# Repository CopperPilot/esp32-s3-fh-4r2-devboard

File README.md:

# ESP32-S3FH4R2 Tiny-LLM Development Board

A compact, 4-layer, breadboard-friendly (`27.00 × 56.20 mm`, `0.9"` / `22.86 mm` row spacing) development board engineered around the **Espressif `ESP32-S3FH4R2`** SoC (`QFN-56 7×7 mm`, **4 MB in-package Quad SPI Flash** + **2 MB in-package Quad SPI PSRAM**) for running embedded LLM inference workloads such as **`llama2.c` (260K-parameter model)** at 240 MHz.

---

## Visual Overview

| Isometric 3D Render | Top Copper & Assembly Render | Bottom Silkscreen & Plane Render |
|---|---|---|
|  |  |  |

---

## Validation & Manufacturing Readiness Summary

| Verification Suite | Tool / Platform | Result | Errors / Dangers | Warnings | Status |
|---|---|---|---|---|---|
| **Schematic ERC** | `kicad-cli sch erc` (KiCad 10.0.4) | **PASS** | `0` | `0` | 100% Clean |
| **Schematic Layout Audit** | CopperPilot `validate_schematic_layout` | **PASS** | `0` | `0` | 100% Clean |
| **PCB Design Rules Check (DRC)** | `kicad-cli pcb drc` (KiCad 10.0.4) | **PASS** | `0` (`0` unconnected) | `0` | 100% Routed (70 nets, 221 pads) |
| **Schematic-to-PCB Netlist Parity** | XML Netlist vs `.kicad_pcb` Audit | **PASS** | `0` mismatches | `0` | 54/54 Footprints, 221/221 Pins Matched |
| **JLCPCB Live DFM (JLCDFM)** | `jlcdfm.com` (27-Check 4-Layer Suite) | **PASS** | **`0` Dangers** | **`0` Warnings** | **27 / 27 Checks Passed** |
| **Lion Circuits Turnkey DFM** | `lioncircuits-order preflight` | **PASS** | `0` | `0` | Meets 6/6 mil, 0.30 mm drill, 6 mil ring |
| **Lion Circuits BOM Scrub** | `order.lioncircuits.com` Live Inventory | **PASS** | `0` Out of Stock | `0` | **28 / 28 BOM Rows Ready to Procure** |

---

## Hardware Architecture

### 1. MCU & In-Package Quad Memory (`U1` — `ESP32-S3FH4R2`)
- **Processor:** Dual-core 32-bit Xtensa LX7 microprocessor running up to **240 MHz** with vector instructions for neural network and DSP acceleration.
- **In-Package Memory:** **4 MB Quad SPI Flash** + **2 MB Quad SPI PSRAM** integrated inside the `7 × 7 mm` `QFN-56` package, powered internally from the 3.3 V `VDD_SPI` domain (Pin 29).
- **Dedicated Internal Memory Pins (Do Not Route Externally):**
  - Pins `28` (`SPICS1` / `GPIO26`), `30` (`SPIHD` / `GPIO27`), `31` (`SPIWP` / `GPIO28`), `32` (`SPICS0` / `GPIO29`), `33` (`SPICLK` / `GPIO30`), `34` (`SPIQ` / `GPIO31`), and `35` (`SPID` / `GPIO32`) are dedicated exclusively to the in-package Quad Flash and Quad PSRAM and are left strictly unconnected (`no_connect`) on both the schematic and PCB.
  - Because the `ESP32-S3FH4R2` uses **4-line Quad SPI** (not 8-line Octal SPI), `GPIO33–GPIO37` (Pins 38–42) and `GPIO47–GPIO48` (Pins 36–37) remain **100% free and available** as general-purpose 3.3 V I/Os, yielding **38 usable GPIOs** in total.

### 2. Clock Generation & 2.4 GHz RF Front-End
- **40 MHz Crystal Oscillator (`Y1`):** Seiko Epson `TSX-3225 40.0000MF15Y-K0` (`3.2 × 2.5 mm` 4-pin SMD, `±10 ppm`, `CL = 12 pF`) placed adjacent to Pins 53/54 (`XTAL_N`/`XTAL_P`) with `15 pF` C0G load capacitors (`C1`, `C2`) and a `24 nH` high-Q series inductor (`L3`, Murata `LQW15AN24NJ00D`) on `XTAL_P` for harmonic suppression.
- **2.4 GHz RF Matching & Antenna (`ANT1`, `J5`):**
  - 50 Ω C-L-C Pi-matching network (`C16 = 1.5 pF`, `L2 = 2.7 nH` Murata `LQG15HS2N7S02D`, `C17 = 1.5 pF`) connected to `LNA_IN` (Pin 1).
  - Edge-mounted 2.4 GHz SMD ceramic chip antenna (`ANT1`, Yageo `ANT3216LL00R2400A`) positioned at the top board edge with a complete **all-layer (`F.Cu`, `In1.Cu`, `In2.Cu`, `B.Cu`) copper and via keep-out zone** (`x = 108.5..114.5 mm`, `y = 99.6..102.8 mm`) and coplanar ground fencing vias.
  - Optional unpopulated `u.FL` coaxial receptacle (`J5`, Hirose `U.FL-R-SMT-1(10)`) via 0 Ω RF path selector pad (`R9`).

### 3. USB 2.0 Type-C & Native USB-Serial/JTAG Programming
- **USB-C Receptacle (`J1`):** GCT `USB4105-GF-A` 16-pin horizontal top-mount USB 2.0 Type-C connector.
- **USB Type-C Sink Configuration:** Independent `5.1 kΩ ±1%` pull-down resistors (`R1` on `CC1`, `R2` on `CC2`) to `GND` for compliant 5 V USB-C upstream host detection across both cable orientations.
- **ESD Protection (`U3`):** STMicroelectronics `USBLC6-2SC6` (`SOT-23-6`) low-capacitance (`2.5 pF typ`) rail-to-rail TVS array protecting `D+`, `D-`, and `VBUS` (`C23 = 100 nF` local `VBUS` bypass at Pin 5).
- **Native USB Data Path:** `D-` (`GPIO19`, Pin 25) and `D+` (`GPIO20`, Pin 26) routed as a matched 90 Ω differential pair through `22 Ω ±1%` series damping resistors (`R5`, `R6`). Supports direct firmware flashing, serial console logging, and JTAG debugging via `idf.py -p <PORT> flash monitor` with no external USB-UART bridge IC required.

### 4. Power Supply & Multi-Domain Decoupling
- **Reverse-Current Protection (`D1`):** Diodes Inc `1N5819HW-7-F` (`40 V`, `1 A` SOD-123 Schottky rectifier) in series between `VBUS` and `+5V`.
- **3.3 V 600 mA LDO Regulator (`U2`):** Diodes Inc `AP2112K-3.3TRG1` (`SOT-23-5`, `600 mA` continuous output, `250 mV` typical dropout at `600 mA`) sized for dual-core 240 MHz execution with simultaneous Wi-Fi/BLE TX bursts.
  - **LDO Input Filtering (`+5V`):** `C20 = 10 µF` (0603 X5R) + `C19 = 100 nF` (0402 X7R).
  - **LDO Output Reservoir (`+3V3`):** `C22 = 22 µF` (0603 X5R) + `C21 = 100 nF` (0402 X7R) + Red 0603 Power-On LED (`D2`, `R7 = 1 kΩ`).
- **Espressif Hardware Design Guideline Decoupling Network:**
  - **`VDD3P3` RF PA Supply (Pins 2, 3):** Pi-filter with `L1 = 2.0 nH` (`LQG15HS2N0S02D`), upstream bulk/bypass `C3 = 10 µF` + `C4 = 1 µF` + `C5 = 100 nF`, and downstream `C6 = 100 nF` right at Pins 2/3.
  - **`VDD3P3_RTC` Supply (Pin 20):** `C7 = 100 nF` local bypass.
  - **`VDD_SPI` In-Package Flash/PSRAM Rail (Pin 29):** `C8 = 1 µF` + `C9 = 100 nF` local decoupling to `GND`.
  - **`VDD3P3_CPU` Digital Core/IO Supply (Pin 46):** `C10 = 1 µF` + `C11 = 100 nF` local bypass.
  - **`VDDA` Analog/PLL/Crystal Supply (Pins 55, 56):** `C12 = 10 µF` + `C13 = 1 µF` + `C14 = 100 nF` + `C15 = 10 nF`.

### 5. Boot/Reset Controls, Strapping Pins & User I/O
- **Chip Enable / Reset (`EN` / `CHIP_PU`, Pin 4):** `R3 = 10 kΩ` pull-up to `+3V3` and `C18 = 1 µF` delay capacitor to `GND` (`τ = 10 ms` power-on reset delay per Espressif datasheet), plus top-actuated SMD tactile `RESET` switch (`SW1`, Omron `B3U-1000P`) to `GND`.
- **Boot Mode Control (`GPIO0`, Pin 5):** `R4 = 10 kΩ` pull-up to `+3V3` and SMD tactile `BOOT` switch (`SW2`, Omron `B3U-1000P`) to `GND`.
- **Safe Strapping Pin Defaults:**
  - `GPIO0` (Pin 5): Pulled high (`10 kΩ` `R4`) for SPI Flash boot; pulled low via `SW2` for Joint Download Boot (USB-Serial/JTAG / UART0).
  - `GPIO3` (Pin 8): Left floating at reset (default JTAG source selection).
  - `GPIO45` (Pin 51): **CRITICAL — Must remain low (unpulled) at reset** so internal weak pull-down selects `VDD_SPI = 3.3 V` for the in-package 3.3 V 4 MB Quad Flash and 2 MB Quad PSRAM.
  - `GPIO46` (Pin 52): Left low at reset via internal weak pull-down.
- **User Status LED (`D3`):** Active-high Green 0603 LED (`LTST-C190KGKT`) with `R8 = 1 kΩ` current-limiting resistor driven by `GPIO38` (Pin 43).
- **Optional I2C OLED Header (`J4`, DNP):** 4-pin 2.54 mm header (`+3V3`, `GND`, `I2C_SCL` on `GPIO9`, `I2C_SDA` on `GPIO8`).

---

## Dual 1×20 Header Pinout (`0.9"` / `22.86 mm` Breadboard Spacing)

All 36 remaining usable GPIOs (plus `EN`, `+3V3`, `+5V`, and `GND`) are broken out to `J2` (Left) and `J3` (Right) with explicit silkscreen labels:

| Pin # | Left Header (`J2`) Signal | MCU Pin / Function | Right Header (`J3`) Signal | MCU Pin / Function | Pin # |
|---|---|---|---|---|---|
| **1** | `+3V3` | 3.3 V LDO Output (`600 mA`) | `+5V` | 5 V Protected USB Rail (via `D1`) | **1** |
| **2** | `EN` | Pin 4 (`CHIP_PU` Active-Low Reset) | `GPIO1` | Pin 6 (`ADC1_CH0` / `TOUCH1`) | **2** |
| **3** | `GPIO4` | Pin 9 (`ADC1_CH3` / `TOUCH4`) | `GPIO2` | Pin 7 (`ADC1_CH1` / `TOUCH2`) | **3** |
| **4** | `GPIO5` | Pin 10 (`ADC1_CH4` / `TOUCH5`) | `U0TXD` | Pin 49 (`GPIO43` / `UART0_TX`) | **4** |
| **5** | `GPIO6` | Pin 11 (`ADC1_CH5` / `TOUCH6`) | `U0RXD` | Pin 50 (`GPIO44` / `UART0_RX`) | **5** |
| **6** | `GPIO7` | Pin 12 (`ADC1_CH6` / `TOUCH7`) | `GPIO42` | Pin 48 (`MTMS` / JTAG TMS) | **6** |
| **7** | `GPIO15` | Pin 21 (`XTAL_32K_P` / `ADC2_CH4`) | `GPIO41` | Pin 47 (`MTDI` / JTAG TDI) | **7** |
| **8** | `GPIO16` | Pin 22 (`XTAL_32K_N` / `ADC2_CH5`) | `GPIO40` | Pin 45 (`MTDO` / JTAG TDO) | **8** |
| **9** | `GPIO17` | Pin 23 (`U1TXD` / `ADC2_CH6`) | `GPIO39` | Pin 44 (`MTCK` / JTAG TCK) | **9** |
| **10** | `GPIO18` | Pin 24 (`U1RXD` / `ADC2_CH7`) | `GPIO38` | Pin 43 (`USER_LED` Active-High) | **10** |
| **11** | `GPIO8` | Pin 13 (`I2C_SDA` / `ADC1_CH7`) | `GPIO37` | Pin 42 (`FSPIQ` — Free on FH4R2) | **11** |
| **12** | `GPIO3` | Pin 8 (`ADC1_CH2` / Strapping) | `GPIO36` | Pin 41 (`FSPICLK` — Free on FH4R2) | **12** |
| **13** | `GPIO46` | Pin 52 (Strapping — Keep Low at Boot) | `GPIO35` | Pin 40 (`FSPID` — Free on FH4R2) | **13** |
| **14** | `GPIO9` | Pin 14 (`I2C_SCL` / `ADC1_CH8`) | `GPIO34` | Pin 39 (`FSPICS0` — Free on FH4R2) | **14** |
| **15** | `GPIO10` | Pin 15 (`FSPICS0` / `ADC1_CH9`) | `GPIO33` | Pin 38 (`FSPIHD` — Free on FH4R2) | **15** |
| **16** | `GPIO11` | Pin 16 (`FSPID` / `ADC2_CH0`) | `GPIO0` | Pin 5 (`BOOT` Button / Strapping) | **16** |
| **17** | `GPIO12` | Pin 17 (`FSPICLK` / `ADC2_CH1`) | `GPIO45` | Pin 51 (`VDD_SPI` Strap — Keep Low!) | **17** |
| **18** | `GPIO13` | Pin 18 (`FSPIQ` / `ADC2_CH2`) | `GPIO48` | Pin 36 (`SPICLK_N` — Free on FH4R2) | **18** |
| **19** | `GPIO14` | Pin 19 (`FSPIWP` / `ADC2_CH3`) | `GPIO47` | Pin 37 (`SPICLK_P` — Free on FH4R2) | **19** |
| **20** | `GND` | Ground Reference | `GPIO21` | Pin 27 (`RTC_GPIO21`) | **20** |

---

## 4-Layer PCB Stackup & Physical Specifications

| Parameter | Specification |
|---|---|
| **Board Dimensions** | `27.00 × 56.20 mm` (`1.063" × 2.213"`), `1.0 mm` corner radius, 4× M2 mounting holes (`H1`–`H4`) |
| **Layer 1 (`F.Cu`)** | Top Signal, 50 Ω RF CPWG feed, 90 Ω USB 2.0 differential pair, component pads + stitched `GND` pour |
| **Layer 2 (`In1.Cu`)** | Unbroken solid `GND` reference plane (with antenna keep-out under `ANT1`) |
| **Layer 3 (`In2.Cu`)** | Solid `+3V3` power distribution plane (with antenna keep-out under `ANT1`) |
| **Layer 4 (`B.Cu`)** | Bottom Signal escape routing + solid stitched `GND` pour and bottom silkscreen artwork |
| **Dielectric Stackup** | `1.6 mm` FR-4 standard 4-layer stackup (`0.10–0.20 mm` prepreg to `In1.Cu` `GND` reference) |
| **Minimum Trace / Space** | `0.155 mm` (`6.1 mil`) signal width (`0.20–0.40 mm` power), `0.1524 mm` (`6.0 mil`) minimum clearance |
| **Via Geometry** | `0.61 mm` pad diameter / `0.30 mm` drill (`0.155 mm` / `6.1 mil` annular ring), 67 vias total |
| **Thermal Design** | `9×` plated thermal vias in `U1` Pad 57 (`4.0 × 4.0 mm` exposed pad) tied directly to `In1.Cu` and `B.Cu` `GND` planes (specify 50–60% windowed stencil paste coverage on `U1` Pad 57 for assembly) |

---

## Bill of Materials (BOM)

The full machine-readable BOM CSVs are provided at [`ESP32S3FH4R2-BOM.csv`](./ESP32S3FH4R2-BOM.csv) (all 28 line items / 50 electrical parts) and [`fab/ESP32S3FH4R2-bom-populated-only.csv`](./fab/ESP32S3FH4R2-bom-populated-only.csv) (25 populated line items / 47 parts).

| Item | Designator | Qty | Value | Package / Footprint | MPN | Manufacturer | LCSC # | Digi-Key # | Status |
|---|---|---|---|---|---|---|---|---|---|
| 1 | `U1` | 1 | `ESP32-S3FH4R2` | `QFN-56-1EP_7x7mm_P0.4mm_EP4x4mm` | `ESP32-S3FH4R2` | Espressif Systems | `C3013940` | `1965-ESP32-S3FH4R2CT-ND` | Populate |
| 2 | `U2` | 1 | `AP2112K-3.3` | `SOT-23-5` | `AP2112K-3.3TRG1` | Diodes Incorporated | `C51118` | `AP2112K-3.3TRG1DICT-ND` | Populate |
| 3 | `U3` | 1 | `USBLC6-2SC6` | `SOT-23-6` | `USBLC6-2SC6` | STMicroelectronics | `C7519` | `497-5235-1-ND` | Populate |
| 4 | `Y1` | 1 | `40MHz` | `Crystal_SMD_3225-4Pin_3.2x2.5mm` | `TSX-3225 40.0000MF15Y-K0` | Seiko Epson | `C255942` | `SER4097CT-ND` | Populate |
| 5 | `ANT1` | 1 | `ANT3216LL00R2400A` | `1206` (`3.2x1.6mm` Chip Antenna) | `ANT3216LL00R2400A` | Yageo / Pulse | `C293767` | `13-ANT3216LL00R2400ACT-ND` | Populate |
| 6 | `J1` | 1 | `USB-C 16P` | `USB_C_Receptacle_GCT_USB4105-xx-A_16P` | `USB4105-GF-A` | GCT | `C165948` | `2073-USB4105-GF-ACT-ND` | Populate |
| 7 | `D1` | 1 | `B5819W` | `D_SOD-123` | `1N5819HW-7-F` | Diodes Incorporated | `C8598` | `1N5819HW-7-FDICT-ND` | Populate |
| 8 | `D2` | 1 | `Red` (PWR) | `LED_0603_1608Metric` | `LTST-C190KRKT` | Lite-On | `C2286` | `160-1447-1-ND` | Populate |
| 9 | `D3` | 1 | `Green` (GPIO38) | `LED_0603_1608Metric` | `LTST-C190KGKT` | Lite-On | `C12624` | `160-1446-1-ND` | Populate |
| 10 | `SW1, SW2` | 2 | `RESET / BOOT` | `SW_SPST_B3U-1000P` | `B3U-1000P` | Omron Electronics | `C145958` | `SW1020CT-ND` | Populate |
| 11 | `L1` | 1 | `2.0nH` | `L_0402_1005Metric` | `LQG15HS2N0S02D` | Murata | `C15132` | `490-14573-1-ND` | Populate |
| 12 | `L2` | 1 | `2.7nH` | `L_0402_1005Metric` | `LQG15HS2N7S02D` | Murata | `C27123` | `490-14577-1-ND` | Populate |
| 13 | `L3` | 1 | `24nH` | `L_0402_1005Metric` | `LQW15AN24NJ00D` | Murata | `C76878` | `490-1155-1-ND` | Populate |
| 14 | `C1, C2` | 2 | `15pF` | `C_0402_1005Metric` | `CC0402JRNPO9BN150` | Yageo | `C1548` | `311-1019-1-ND` | Populate |
| 15 | `C16, C17` | 2 | `1.5pF` | `C_0402_1005Metric` | `CC0402CRNPO9BN1R5` | Yageo | `C1552` | `311-1010-1-ND` | Populate |
| 16 | `C15` | 1 | `10nF` | `C_0402_1005Metric` | `CL05B103KB5NNNC` | Samsung Electro-Mechanics | `C15195` | `1276-1009-1-ND` | Populate |
| 17 | `C5–C7, C9, C11, C14, C19, C21, C23` | 9 | `100nF` | `C_0402_1005Metric` | `CL05B104KO5NNNC` | Samsung Electro-Mechanics | `C1525` | `1276-1000-1-ND` | Populate |
| 18 | `C4, C8, C10, C13, C18` | 5 | `1uF` | `C_0402_1005Metric` | `CL05A105KP5NNNC` | Samsung Electro-Mechanics | `C52923` | `1276-1006-1-ND` | Populate |
| 19 | `C3, C12` | 2 | `10uF` (6.3V) | `C_0402_1005Metric` | `CL05A106MQ5NUNC` | Samsung Electro-Mechanics | `C15525` | `1276-1089-1-ND` | Populate |
| 20 | `C20` | 1 | `10uF` (10V) | `C_0603_1608Metric` | `CL10A106MP8NNNC` | Samsung Electro-Mechanics | `C19702` | `1276-1099-1-ND` | Populate |
| 21 | `C22` | 1 | `22uF` (10V) | `C_0603_1608Metric` | `CL10A226MP8NUNE` | Samsung Electro-Mechanics | `C59461` | `1276-1119-1-ND` | Populate |
| 22 | `R1, R2` | 2 | `5.1k` | `R_0402_1005Metric` | `RC0402FR-075K1L` | Yageo | `C25905` | `311-5.10KLRCT-ND` | Populate |
| 23 | `R3, R4` | 2 | `10k` | `R_0402_1005Metric` | `RC0402FR-0710KL` | Yageo | `C25744` | `311-10.0KLRCT-ND` | Populate |
| 24 | `R5, R6` | 2 | `22` | `R_0402_1005Metric` | `RC0402FR-0722RL` | Yageo | `C25092` | `311-22.0LRCT-ND` | Populate |
| 25 | `R7, R8` | 2 | `1k` | `R_0402_1005Metric` | `RC0402FR-071KL` | Yageo | `C11702` | `311-1.00KLRCT-ND` | Populate |
| 26 | `J2, J3` | 2 | `HEADER_1x20` | `PinHeader_1x20_P2.54mm_Vertical` | `M20-9992046` | Harwin | `C2839521` | `952-2273-ND` | Populate |
| 27 | `J4` | 1 | `I2C_OLED_DNP` | `PinHeader_1x04_P2.54mm_Vertical` | `TSW-104-07-L-S` | Samtec | `C2839481` | `SAM1029-04-ND` | DNP |
| 28 | `J5` | 1 | `U.FL_DNP` | `U.FL_Hirose_U.FL-R-SMT-1_Vertical` | `U.FL-R-SMT-1(10)` | Hirose Electric | `C88373` | `H9161CT-ND` | DNP |
| 29 | `R9` | 1 | `0R_DNP` | `R_0402_1005Metric` | `RC0402JR-070RL` | Yageo | `C17168` | `311-0.0LRCT-ND` | DNP |

---

## Repository Structure & Engineering Documentation

### Primary KiCad 10 Design Files
- [`ESP32S3FH4R2.kicad_pro`](./ESP32S3FH4R2.kicad_pro) — KiCad 10 project configuration & DRC rules (`0.1524 mm` clearance, `0.155 mm` min track, `0.61/0.30 mm` vias).
- [`ESP32S3FH4R2.kicad_sch`](./ESP32S3FH4R2.kicad_sch) — Single-sheet hierarchical-framed schematic (`run_erc`: 0 errors, 0 warnings).
- [`ESP32S3FH4R2.kicad_pcb`](./ESP32S3FH4R2.kicad_pcb) — 4-layer routed PCB layout (`run_drc`: 0 errors, 0 warnings, 0 unconnected items).

### Ready-to-Upload Fabrication & Assembly Packages
- [`ESP32S3FH4R2-gerbers.zip`](./ESP32S3FH4R2-gerbers.zip) (also in [`fab/ESP32S3FH4R2-gerbers.zip`](./fab/ESP32S3FH4R2-gerbers.zip)) — 14-file 4-layer Gerber + Excellon drill archive verified on JLCPCB JLCDFM (`27/27 PASS`) and Lion Circuits.
- [`fab/ESP32S3FH4R2-gerbers-with-drill-maps.zip`](./fab/ESP32S3FH4R2-gerbers-with-drill-maps.zip) — Complete Gerber + Excellon archive bundled with Gerber X2 and PDF drill maps (`fab/gerbers/`).
- [`ESP32S3FH4R2-BOM.csv`](./ESP32S3FH4R2-BOM.csv) & [`fab/ESP32S3FH4R2-bom-populated-only.csv`](./fab/ESP32S3FH4R2-bom-populated-only.csv) — Turnkey PCBA Bill of Materials CSVs.
- [`ESP32S3FH4R2-CPL-XY.csv`](./ESP32S3FH4R2-CPL-XY.csv) & [`fab/ESP32S3FH4R2-cpl-populated-only.csv`](./fab/ESP32S3FH4R2-cpl-populated-only.csv) — Pick-and-Place XY Centroid CSVs.

### Engineering Notes, Validation Reports & Provenance (`.copperpilot/`)
- **Consolidated DFM & Validation Report:** [`.copperpilot/notes/final-dfm-validation-report.md`](./.copperpilot/notes/final-dfm-validation-report.md)
- **Multidisciplinary Board Validation Audit (SI/PI/EMC/Thermal/DFM/IPC):** [`.copperpilot/notes/board-validation-report.md`](./.copperpilot/notes/board-validation-report.md)
- **Final Design Deliverables, Pinout & BOM Guide:** [`.copperpilot/notes/final-design-deliverables.md`](./.copperpilot/notes/final-design-deliverables.md)
- **Lion Circuits DFM & Live Inventory Report:** [`.copperpilot/notes/lioncircuits-dfm-bom-report.md`](./.copperpilot/notes/lioncircuits-dfm-bom-report.md)
- **Manufacturing Export File Manifest:** [`.copperpilot/notes/manufacturing-export-files.md`](./.copperpilot/notes/manufacturing-export-files.md)
- **ESP32-S3FH4R2 Datasheet & Pinout Reference:** [`.copperpilot/notes/esp32s3fh4r2-hardware-reference.md`](./.copperpilot/notes/esp32s3fh4r2-hardware-reference.md)
- **LCSC & Digi-Key Component Sourcing Reference:** [`.copperpilot/notes/esp32s3fh4r2-bom-sourcing.md`](./.copperpilot/notes/esp32s3fh4r2-bom-sourcing.md)
- **Schematic Review & Drafting Cleanup Log:** [`.copperpilot/notes/schematic-review-and-cleanup.md`](./.copperpilot/notes/schematic-review-and-cleanup.md)
- **KiCad 10 Library & 3D Model Audit:** [`.copperpilot/notes/kicad10-library-survey.md`](./.copperpilot/notes/kicad10-library-survey.md)
- **Hardware Implementation Plan:** [`.copperpilot/plans/esp32s3fh4r2-llm-dev-board.plan.md`](./.copperpilot/plans/esp32s3fh4r2-llm-dev-board.plan.md)
- **Design Oracle & Gate Records:** [`.copperpilot/oracle/design-oracle.json`](./.copperpilot/oracle/design-oracle.json), [`.copperpilot/oracle/provenance.jsonl`](./.copperpilot/oracle/provenance.jsonl), [`.copperpilot/oracle/gates.json`](./.copperpilot/oracle/gates.json)

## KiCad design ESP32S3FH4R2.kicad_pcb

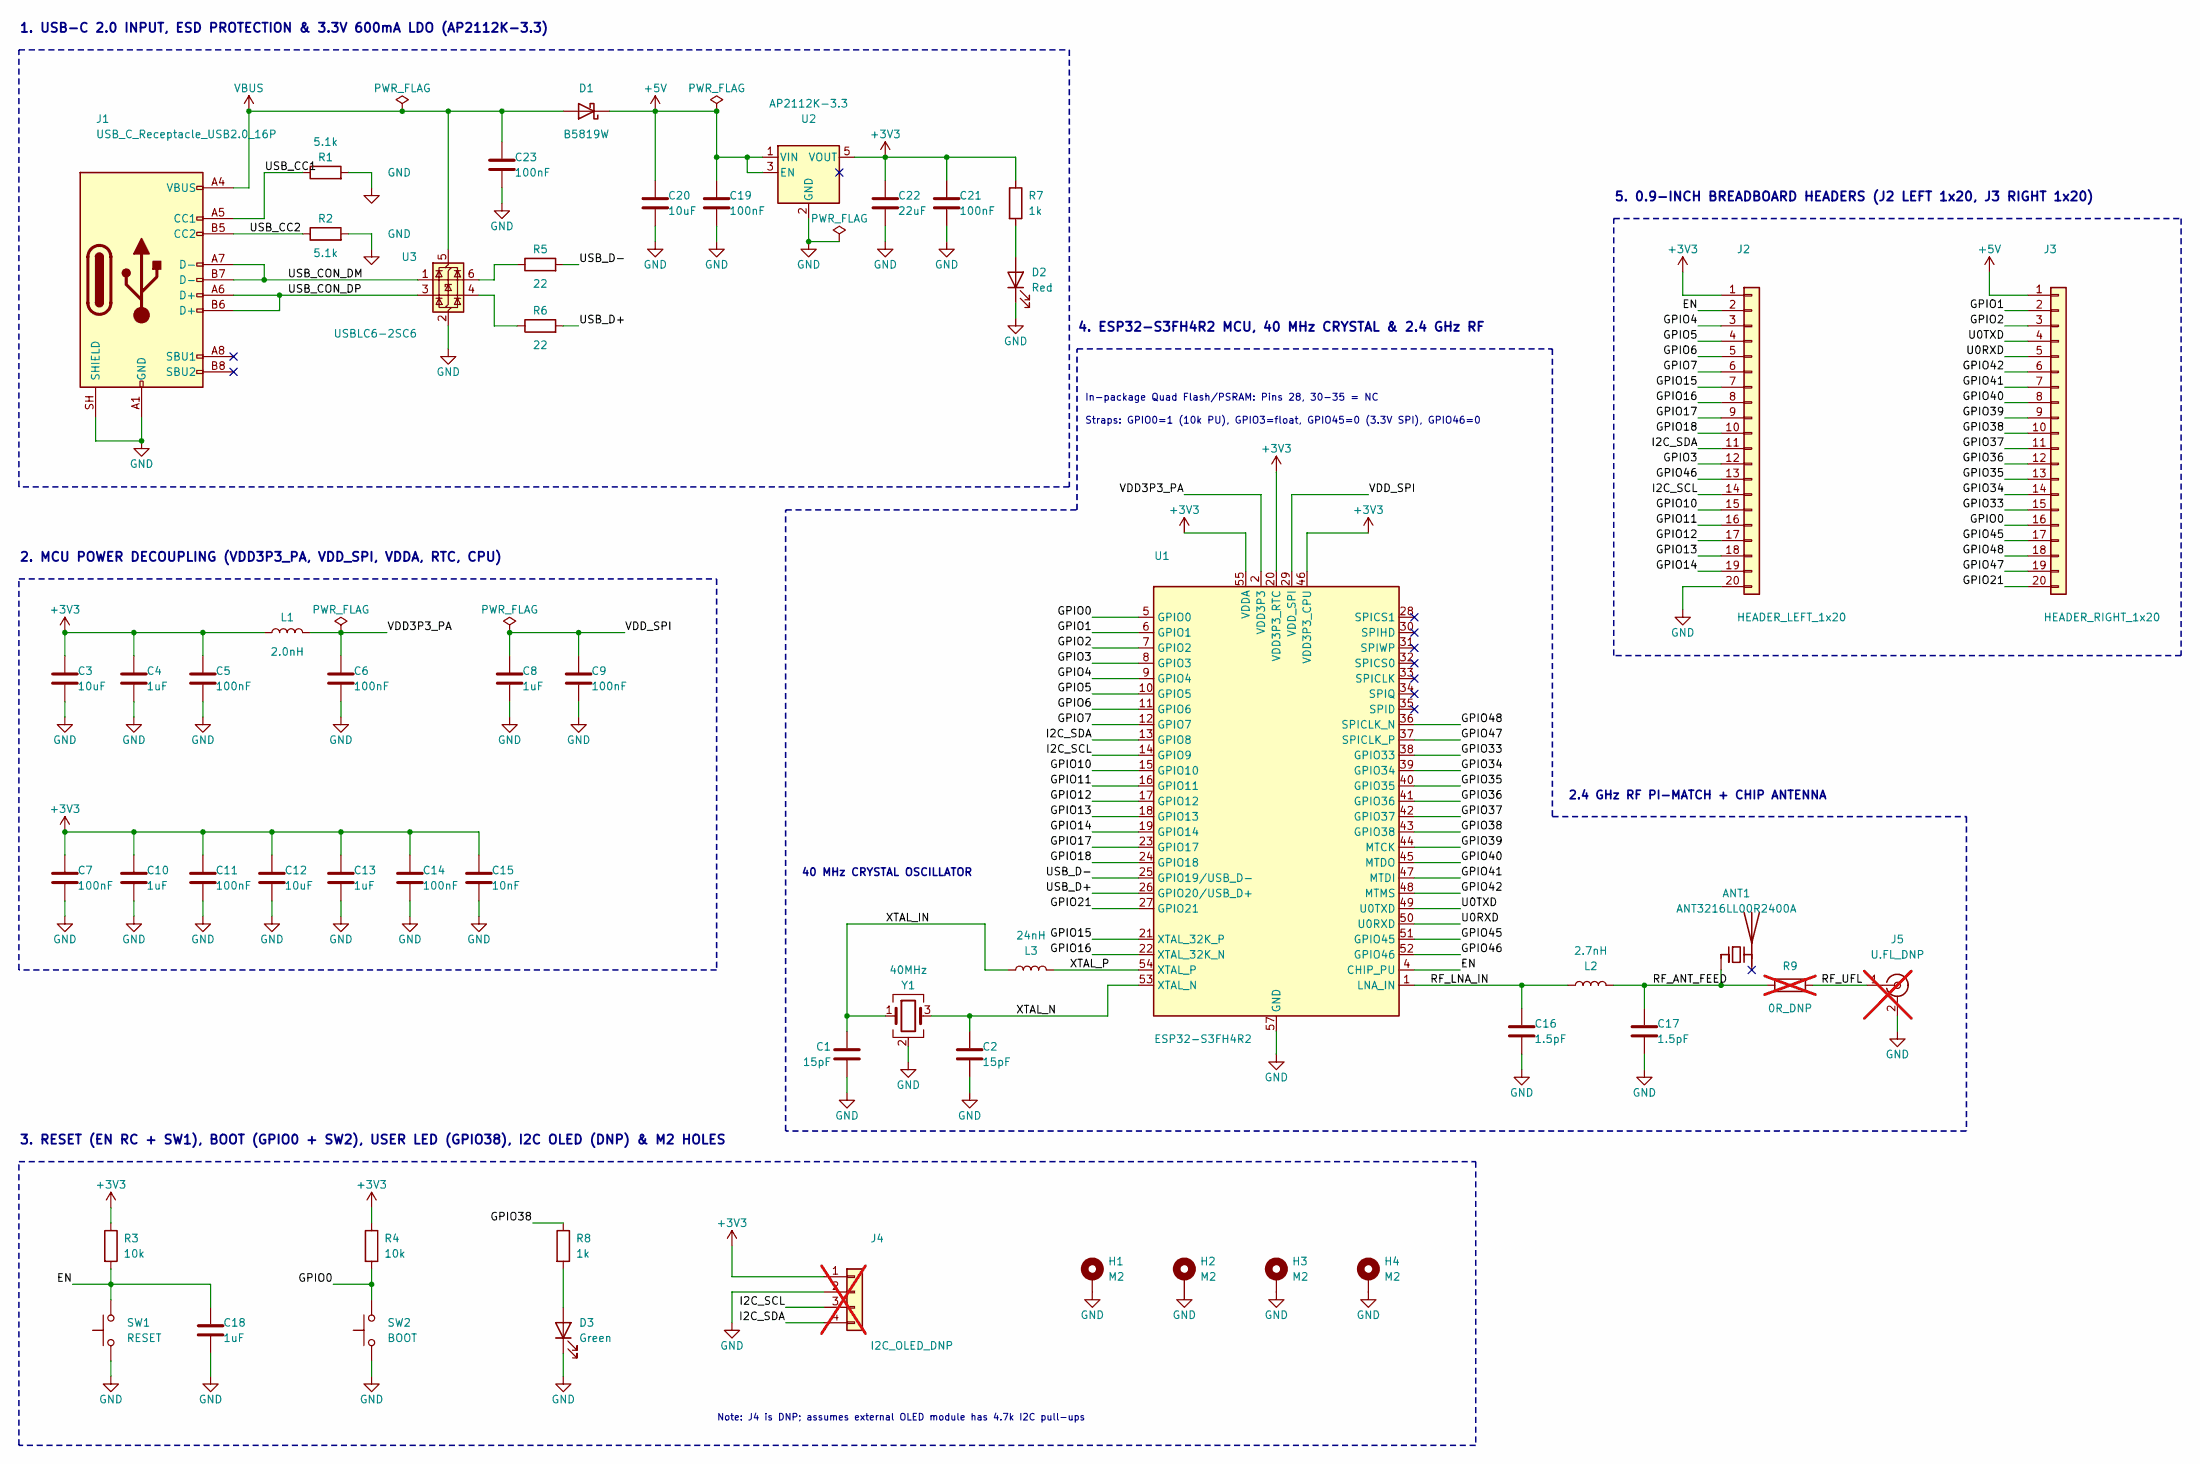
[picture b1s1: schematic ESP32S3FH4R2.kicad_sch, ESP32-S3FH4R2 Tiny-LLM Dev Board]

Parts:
ANT1: ANT3216LL00R2400A; Johanson_2450AT18x100; MPN ANT3216LL00R2400A; LCSC C293767
C1, C2: 15pF; C_0402_1005Metric; MPN CC0402JRNPO9BN150; LCSC C1548
C3, C12: 10uF; C_0402_1005Metric; MPN CL05A106MQ5NUNC; LCSC C15525
C4, C8, C10, C13, C18: 1uF; C_0402_1005Metric; MPN CL05A105KP5NNNC; LCSC C52923
C5, C6, C7, C9, C11, C14, C19, C21, C23: 100nF; C_0402_1005Metric; MPN CL05B104KO5NNNC; LCSC C1525
C15: 10nF; C_0402_1005Metric; MPN CL05B103KB5NNNC; LCSC C15195
C16, C17: 1.5pF; C_0402_1005Metric; MPN CC0402CRNPO9BN1R5; LCSC C1552
C20: 10uF; C_0603_1608Metric; MPN CL10A106MP8NNNC; LCSC C19702
C22: 22uF; C_0603_1608Metric; MPN CL10A226MP8NUNE; LCSC C59461
D1: B5819W; D_SOD-123; MPN 1N5819HW-7-F; LCSC C8598
D2: Red; LED_0603_1608Metric; MPN LTST-C190KRKT; LCSC C2286
D3: Green; LED_0603_1608Metric; MPN LTST-C190KGKT; LCSC C12624
H1, H2, H3, H4: M2; MountingHole_2.2mm_M2_Pad_Via
J1: USB_C_Receptacle_USB2.0_16P; USB_C_Receptacle_GCT_USB4105-xx-A_16P_TopMnt_Horizontal; MPN USB4105-GF-A; LCSC C165948
J2: HEADER_LEFT_1x20; PinHeader_1x20_P2.54mm_Vertical; MPN M20-9992046; LCSC C2839521
J3: HEADER_RIGHT_1x20; PinHeader_1x20_P2.54mm_Vertical; MPN M20-9992046; LCSC C2839521
J4: I2C_OLED_DNP; PinHeader_1x04_P2.54mm_Vertical; MPN TSW-104-07-L-S; LCSC C2839481; not fitted
J5: U.FL_DNP; U.FL_Hirose_U.FL-R-SMT-1_Vertical; MPN U.FL-R-SMT-1(10); LCSC C88374; not fitted
L1: 2.0nH; L_0402_1005Metric; MPN LQG15HS2N0S02D; LCSC C104109
L2: 2.7nH; L_0402_1005Metric; MPN LQG15HS2N7S02D; LCSC C27123
L3: 24nH; L_0402_1005Metric; MPN LQW15AN24NJ00D; LCSC C76912
R1, R2: 5.1k; R_0402_1005Metric; MPN RC0402FR-075K1L; LCSC C25905
R3, R4: 10k; R_0402_1005Metric; MPN RC0402FR-0710KL; LCSC C25744
R5, R6: 22; R_0402_1005Metric; MPN RC0402FR-0722RL; LCSC C25092
R7, R8: 1k; R_0402_1005Metric; MPN RC0402FR-071KL; LCSC C11702
R9: 0R_DNP; R_0402_1005Metric; MPN RC0402JR-070RL; LCSC C17168; not fitted
SW1: RESET; SW_SPST_B3U-1000P; MPN B3U-1000P; LCSC C145958
SW2: BOOT; SW_SPST_B3U-1000P; MPN B3U-1000P; LCSC C145958
U1: ESP32-S3FH4R2; QFN-56-1EP_7x7mm_P0.4mm_EP4x4mm_ThermalVias; MPN ESP32-S3FH4R2; LCSC C3013940
U2: AP2112K-3.3; SOT-23-5; MPN AP2112K-3.3TRG1; LCSC C51118
U3: USBLC6-2SC6; SOT-23-6; MPN USBLC6-2SC6; LCSC C7519
Y1: 40MHz; Crystal_SMD_3225-4Pin_3.2x2.5mm; MPN TSX-3225 40.0000MF15Y-K0; LCSC C255942

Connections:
+3V3: C3.1, C4.1, C5.1, C7.1, C10.1, C11.1, C12.1, C13.1, C14.1, C15.1, C21.1, C22.1, J2.1, J4.1, L1.1, R3.1, R4.1, R7.1, U1.20 (VDD3P3_RTC), U1.46 (VDD3P3_CPU), U1.55 (VDDA), U1.56 (VDDA), U2.5 (VOUT)
+5V: C19.1, C20.1, D1.1 (K), J3.1, U2.1 (VIN), U2.3 (EN)
/EN: C18.1, J2.2, R3.2, SW1.2, U1.4 (CHIP_PU)
/GPIO0: J3.16, R4.2, SW2.2, U1.5 (GPIO0)
/GPIO1: J3.2, U1.6 (GPIO1)
/GPIO2: J3.3, U1.7 (GPIO2)
/GPIO3: J2.12, U1.8 (GPIO3)
/GPIO4: J2.3, U1.9 (GPIO4)
/GPIO5: J2.4, U1.10 (GPIO5)
/GPIO6: J2.5, U1.11 (GPIO6)
/GPIO7: J2.6, U1.12 (GPIO7)
/GPIO10: J2.15, U1.15 (GPIO10)
/GPIO11: J2.16, U1.16 (GPIO11)
/GPIO12: J2.17, U1.17 (GPIO12)
/GPIO13: J2.18, U1.18 (GPIO13)
/GPIO14: J2.19, U1.19 (GPIO14)
/GPIO15: J2.7, U1.21 (XTAL_32K_P)
/GPIO16: J2.8, U1.22 (XTAL_32K_N)
/GPIO17: J2.9, U1.23 (GPIO17)
/GPIO18: J2.10, U1.24 (GPIO18)
/GPIO21: J3.20, U1.27 (GPIO21)
/GPIO33: J3.15, U1.38 (GPIO33)
/GPIO34: J3.14, U1.39 (GPIO34)
/GPIO35: J3.13, U1.40 (GPIO35)
/GPIO36: J3.12, U1.41 (GPIO36)
/GPIO37: J3.11, U1.42 (GPIO37)
/GPIO38: J3.10, R8.1, U1.43 (GPIO38)
/GPIO39: J3.9, U1.44 (MTCK)
/GPIO40: J3.8, U1.45 (MTDO)
/GPIO41: J3.7, U1.47 (MTDI)
/GPIO42: J3.6, U1.48 (MTMS)
/GPIO45: J3.17, U1.51 (GPIO45)
/GPIO46: J2.13, U1.52 (GPIO46)
/GPIO47: J3.19, U1.37 (SPICLK_P)
/GPIO48: J3.18, U1.36 (SPICLK_N)
/I2C_SCL: J2.14, J4.3, U1.14 (GPIO9)
/I2C_SDA: J2.11, J4.4, U1.13 (GPIO8)
/RF_ANT_FEED: ANT1.1 (FEED), C17.1, L2.2, R9.1
/RF_LNA_IN: C16.1, L2.1, U1.1 (LNA_IN)
/RF_UFL: J5.1 (In), R9.2
/U0RXD: J3.5, U1.50 (U0RXD)
/U0TXD: J3.4, U1.49 (U0TXD)
/USB_CC1: J1.A5 (CC1), R1.1
/USB_CC2: J1.B5 (CC2), R2.1
/USB_CON_DM: J1.A7 (D-), J1.B7 (D-), U3.1 (I/O1)
/USB_CON_DP: J1.A6 (D+), J1.B6 (D+), U3.3 (I/O2)
/USB_D+: R6.2, U1.26 (GPIO20/USB_D+)
/USB_D-: R5.2, U1.25 (GPIO19/USB_D-)
/VDD3P3_PA: C6.1, L1.2, U1.2 (VDD3P3), U1.3 (VDD3P3)
/VDD_SPI: C8.1, C9.1, U1.29 (VDD_SPI)
/XTAL_IN: C1.1, L3.1, Y1.1
/XTAL_N: C2.1, U1.53 (XTAL_N), Y1.3
/XTAL_P: L3.2, U1.54 (XTAL_P)
GND: C1.2, C2.2, C3.2, C4.2, C5.2, C6.2, C7.2, C8.2, C9.2, C10.2, C11.2, C12.2, C13.2, C14.2, C15.2, C16.2, C17.2, C18.2, C19.2, C20.2, C21.2, C22.2, C23.2, D2.1 (K), D3.1 (K), H1.1, H2.1, H3.1, H4.1, J1.A1 (GND), J1.A12 (GND), J1.B1 (GND), J1.B12 (GND), J1.SH (SHIELD), J2.20, J4.2, J5.2 (Ext), R1.2, R2.2, SW1.1, SW2.1, U1.57 (GND), U2.2 (GND), U3.2 (GND), Y1.2 (G), Y1.4 (G)
unnamed: D2.2 (A), R7.2
unnamed: D3.2 (A), R8.2
unnamed: R5.1, U3.6 (I/O1)
unnamed: R6.1, U3.4 (I/O2)
VBUS: C23.1, D1.2 (A), J1.A4 (VBUS), J1.A9 (VBUS), J1.B4 (VBUS), J1.B9 (VBUS), U3.5 (VBUS)

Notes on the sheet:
1. USB-C 2.0 INPUT, ESD PROTECTION & 3.3V 600mA LDO (AP2112K-3.3)
2. MCU POWER DECOUPLING (VDD3P3_PA, VDD_SPI, VDDA, RTC, CPU)
3. RESET (EN RC + SW1), BOOT (GPIO0 + SW2), USER LED (GPIO38), I2C OLED (DNP) & M2 HOLES
Note: J4 is DNP; assumes external OLED module has 4.7k I2C pull-ups
40 MHz CRYSTAL OSCILLATOR
2.4 GHz RF PI-MATCH + CHIP ANTENNA
4. ESP32-S3FH4R2 MCU, 40 MHz CRYSTAL & 2.4 GHz RF
In-package Quad Flash/PSRAM: Pins 28, 30-35 = NC
Straps: GPIO0=1 (10k PU), GPIO3=float, GPIO45=0 (3.3V SPI), GPIO46=0
5. 0.9-INCH BREADBOARD HEADERS (J2 LEFT 1x20, J3 RIGHT 1x20)

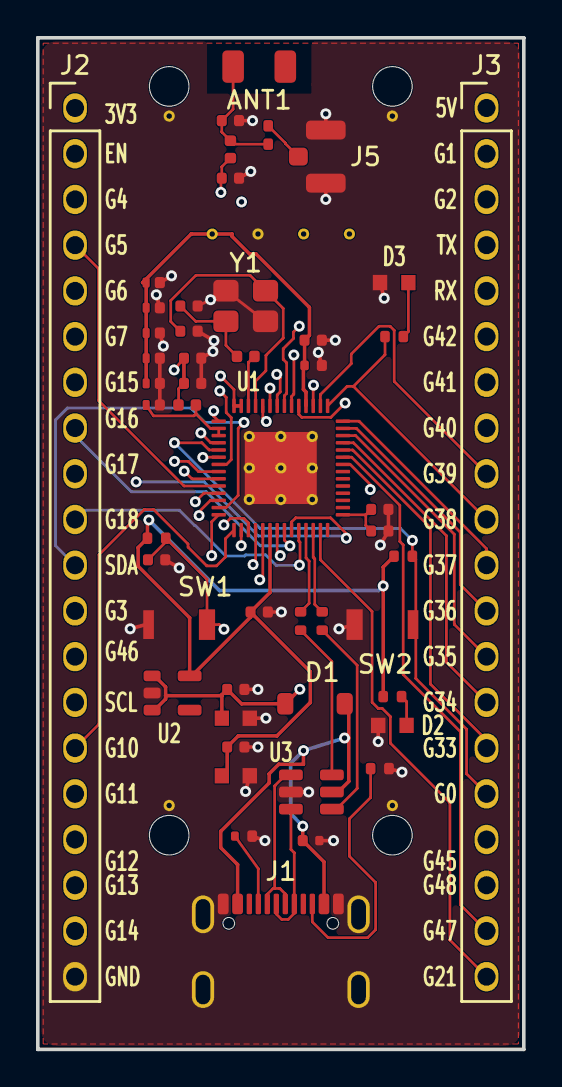
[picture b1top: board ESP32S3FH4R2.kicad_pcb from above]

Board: 4 copper layers, 27.0 x 56.2 mm, 54 parts (0 on the bottom side), 59 nets.

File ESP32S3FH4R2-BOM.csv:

Item Number,Designator,Unit Quantity,Description,MPN,Manufacturer,Footprint,Value,LCSC Part #,Digi-Key Part #,Assembly Instructions
1,U1,1,2.4 GHz Wi-Fi + BLE 5.0 Dual-Core LX7 SoC with 4 MB Quad SPI Flash and 2 MB Quad PSRAM,ESP32-S3FH4R2,Espressif Systems,QFN-56-1EP_7x7mm_P0.4mm_EP4x4mm_ThermalVias,ESP32-S3FH4R2,C3013940,1965-ESP32-S3FH4R2CT-ND,Populate
2,U2,1,Fixed 3.3V 600mA Low-Dropout Linear Regulator,AP2112K-3.3TRG1,Diodes Incorporated,SOT-23-5,AP2112K-3.3,C51118,AP2112K-3.3TRG1DICT-ND,Populate
3,U3,1,Very Low Capacitance ESD Protection Array for USB 2.0,USBLC6-2SC6,STMicroelectronics,SOT-23-6,USBLC6-2SC6,C7519,497-5235-1-ND,Populate
4,Y1,1,40.000 MHz 10ppm 12pF SMD 3225 4-Pin Quartz Crystal,TSX-3225 40.0000MF15Y-K0,Seiko Epson,Crystal_SMD_3225-4Pin_3.2x2.5mm,40MHz,C255942,SER4097CT-ND,Populate
5,ANT1,1,2.4 GHz 50 Ohm SMD Ceramic Chip Antenna (3.2x1.6mm),ANT3216LL00R2400A,Yageo / Pulse,Johanson_2450AT18x100,ANT3216LL00R2400A,C293767,13-ANT3216LL00R2400ACT-ND,Populate
6,J1,1,USB Type-C 16-Pin USB 2.0 Right-Angle SMD Receptacle,USB4105-GF-A,Global Connector Technology,USB_C_Receptacle_GCT_USB4105-xx-A_16P_TopMnt_Horizontal,USB_C_Receptacle_USB2.0_16P,C165948,2073-USB4105-GF-ACT-ND,Populate
7,D1,1,40V 1A Schottky Barrier Rectifier Diode,1N5819HW-7-F,Diodes Incorporated,D_SOD-123,B5819W,C8598,1N5819HW-7-FDICT-ND,Populate
8,D2,1,Red 0603 SMD Power Indicator LED,LTST-C190KRKT,Lite-On,LED_0603_1608Metric,Red,C2286,160-1447-1-ND,Populate
9,D3,1,Green 0603 SMD User Status LED (GPIO38),LTST-C190KGKT,Lite-On,LED_0603_1608Metric,Green,C12624,160-1446-1-ND,Populate
10,"SW1, SW2",2,"SPST-NO Ultraminiature Top-Actuated SMD Tactile Switch (RESET, BOOT)",B3U-1000P,Omron Electronics,SW_SPST_B3U-1000P,RESET / BOOT,C145958,SW1020CT-ND,Populate
11,L1,1,2.0nH +/-0.3nH 0402 High-Q RF Inductor (VDD3P3 PA Filter),LQG15HS2N0S02D,Murata,L_0402_1005Metric,2.0nH,C104109,490-14573-1-ND,Populate
12,L2,1,2.7nH +/-0.3nH 0402 High-Q RF Matching Inductor (50 Ohm Pi-Match),LQG15HS2N7S02D,Murata,L_0402_1005Metric,2.7nH,C27123,490-14577-1-ND,Populate
13,L3,1,24nH 5% 0402 Wirewound RF Inductor (XTAL_P Harmonic Suppression),LQW15AN24NJ00D,Murata,L_0402_1005Metric,24nH,C76912,490-1155-1-ND,Populate
14,"C1, C2",2,15pF 50V 5% C0G/NP0 0402 Ceramic Crystal Load Capacitor,CC0402JRNPO9BN150,Yageo,C_0402_1005Metric,15pF,C1548,311-1019-1-ND,Populate
15,"C16, C17",2,1.5pF 50V +/-0.25pF C0G/NP0 0402 RF Matching Shunt Capacitor,CC0402CRNPO9BN1R5,Yageo,C_0402_1005Metric,1.5pF,C1552,311-1010-1-ND,Populate
16,C15,1,10nF 50V 10% X7R 0402 Ceramic Decoupling Capacitor (VDDA),CL05B103KB5NNNC,Samsung Electro-Mechanics,C_0402_1005Metric,10nF,C15195,1276-1009-1-ND,Populate
17,"C5, C6, C7, C9, C11, C14, C19, C21, C23",9,100nF 16V 10% X7R 0402 Ceramic Decoupling Capacitor,CL05B104KO5NNNC,Samsung Electro-Mechanics,C_0402_1005Metric,100nF,C1525,1276-1000-1-ND,Populate
18,"C4, C8, C10, C13, C18",5,1uF 10V 10% X5R 0402 Ceramic Decoupling & EN RC Delay Capacitor,CL05A105KP5NNNC,Samsung Electro-Mechanics,C_0402_1005Metric,1uF,C52923,1276-1006-1-ND,Populate
19,"C3, C12",2,"10uF 6.3V 20% X5R 0402 Ceramic Bulk Capacitor (VDD3P3, VDDA)",CL05A106MQ5NUNC,Samsung Electro-Mechanics,C_0402_1005Metric,10uF,C15525,1276-1089-1-ND,Populate
20,C20,1,10uF 10V 20% X5R 0603 Ceramic LDO Input Bulk Capacitor (+5V),CL10A106MP8NNNC,Samsung Electro-Mechanics,C_0603_1608Metric,10uF,C19702,1276-1099-1-ND,Populate
21,C22,1,22uF 10V 20% X5R 0603 Ceramic LDO Output Bulk Reservoir Capacitor,CL10A226MP8NUNE,Samsung Electro-Mechanics,C_0603_1608Metric,22uF,C59461,1276-1119-1-ND,Populate
22,"R1, R2",2,5.1k Ohm 1% 1/16W 0402 Thick Film Resistor (USB-C CC1/CC2 Rd),RC0402FR-075K1L,Yageo,R_0402_1005Metric,5.1k,C25905,311-5.10KLRCT-ND,Populate
23,"R3, R4",2,"10k Ohm 1% 1/16W 0402 Thick Film Pull-Up Resistor (EN, GPIO0)",RC0402FR-0710KL,Yageo,R_0402_1005Metric,10k,C25744,311-10.0KLRCT-ND,Populate
24,"R5, R6",2,22 Ohm 1% 1/16W 0402 Thick Film USB D+/D- Series Resistor,RC0402FR-0722RL,Yageo,R_0402_1005Metric,22,C25092,311-22.0LRCT-ND,Populate
25,"R7, R8",2,1k Ohm 1% 1/16W 0402 Thick Film LED Current-Limiting Resistor,RC0402FR-071KL,Yageo,R_0402_1005Metric,1k,C11702,311-1.00KLRCT-ND,Populate
26,"J2, J3",2,1x20 2.54mm Pitch Vertical Through-Hole Pin Header,M20-9992046,Harwin,PinHeader_1x20_P2.54mm_Vertical,HEADER_1x20,C2839521,952-2273-ND,Populate
27,J4,1,1x04 2.54mm Pitch Vertical Through-Hole I2C OLED Header (Optional),TSW-104-07-L-S,Samtec,PinHeader_1x04_P2.54mm_Vertical,I2C_OLED_DNP,C2839481,SAM1029-04-ND,DNP
28,J5,1,DC-6GHz 50 Ohm U.FL Coaxial SMT RF Receptacle (Optional),U.FL-R-SMT-1(10),Hirose Electric,U.FL_Hirose_U.FL-R-SMT-1_Vertical,U.FL_DNP,C88374,H9161CT-ND,DNP
29,R9,1,0 Ohm Jumper 0402 RF Path Selector to J5 (Optional),RC0402JR-070RL,Yageo,R_0402_1005Metric,0R_DNP,C17168,311-0.0LRCT-ND,DNP
